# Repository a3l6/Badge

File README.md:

# Hack Canada Badge — v2 (RP2040 + E-Paper)

This was the first serious attempt at the Hack Canada badge before the design was later simplified into the battery-free NFC badges of v3 and v4.

> The main render shows all 51 components placed at their real board positions with the 2.13" e-paper panel mounted on top. Renders are generated from this version's Gerber files (`pcb/prod/gerber/`); colours and the on-screen layout are illustrative.

---

## What it is

Where the later revisions stripped everything down to a passive NFC tag, v2 aimed high: a programmable badge with a screen you could actually put graphics and text on. It's essentially a tiny RP2040 development board in badge form, with an e-paper panel, USB-C for power and programming, and external flash for firmware and assets.

## How it works

```
USB-C ──► RP2040 ──► SPI ──► 2.13" e-paper display (GDEY0213F51)
            │
            ├──► QSPI ──► W25Q32 flash (firmware + images)
            ├──► 12 MHz crystal
            ├──► BOOT + RESET buttons, SWD header
            └──► status LED
```

Plug it in over USB-C, flash firmware to the RP2040 (BOOTSEL/UF2 or SWD), and drive the e-paper display to show a name, schedule, or artwork. The display holds its image with no power, which suits a badge that spends most of its life idle.

## Core components

| Function | Part |
| --- | --- |
| Microcontroller | RP2040 |
| Display | GDEY0213F51 — 2.13" e-paper / E-Ink (SEEKINK panel) |
| Flash | W25Q32JVSSIQ — 32 Mbit (4 MB) SPI/QSPI |
| Clock | 12 MHz crystal (FC4SDCBMF12.0-T1) |
| Power / data | USB Type-C |
| Indicator | VLMC3100-GS08 LED |
| Protection | LESD5D5.0CT1G TVS/ESD diodes |
| Controls | BOOT + RESET buttons, SWD debug header |

## Board

| Spec | Value |
| --- | --- |
| Dimensions | 77.05 × 86.55 mm |
| Layers | 2 |
| Thickness | 1.6 mm |
| Designed in | KiCad 8 |

| Front | Back |
| --- | --- |
|  |  |

### Assembled (parts placed)

The e-paper panel (shown mounted in the main image at the top) connects over the FPC ribbon connector at the upper-left and sits above the board across the open top area, with the RP2040 and power circuitry tucked below it. The on-screen layout in that render is a placeholder mock-up, not artwork from the repo.

## Repository layout (v2 branch)

```
pcb/
├── badge.kicad_pcb / .kicad_sch / .kicad_pro   # main design
├── prod/gerber/                                # Gerbers, drills, gbrjob — ready to fab
├── badge-backups/                              # KiCad auto-backups
├── <component>/                                # per-part symbol/footprint/3D libraries
│   (RP2040, W25Q32, GDEY0213F51, crystal, LEDs, TVS, caps …)
└── assets/                                     # logos
GDEY0213F51.kicad_sym                           # e-paper display symbol
README.md
```

## Building your own

1. **Fabricate:** send `pcb/prod/gerber/` (or `badge-gerbers-and-designs.zip`) to your board house. It's a 2-layer, 1.6 mm board.
2. **Edit:** open `pcb/badge.kicad_pro` in KiCad 8 to modify the layout or schematic.
3. **Assemble & flash:** populate the parts, power over USB-C, and load RP2040 firmware via UF2 (BOOTSEL) or the SWD header. Then drive the GDEY0213F51 over SPI.

## History

v2 → **v3** (pivot to a battery-free NFC badge, adopted from the open "Opentaxus" design) → **v4** (streamlined 4-part NFC badge). See the `v3` and `v4` branches / READMEs.

## License

No license file is included, so all rights are reserved by default. Contact [@a3l6](https://github.com/a3l6) to discuss reuse.

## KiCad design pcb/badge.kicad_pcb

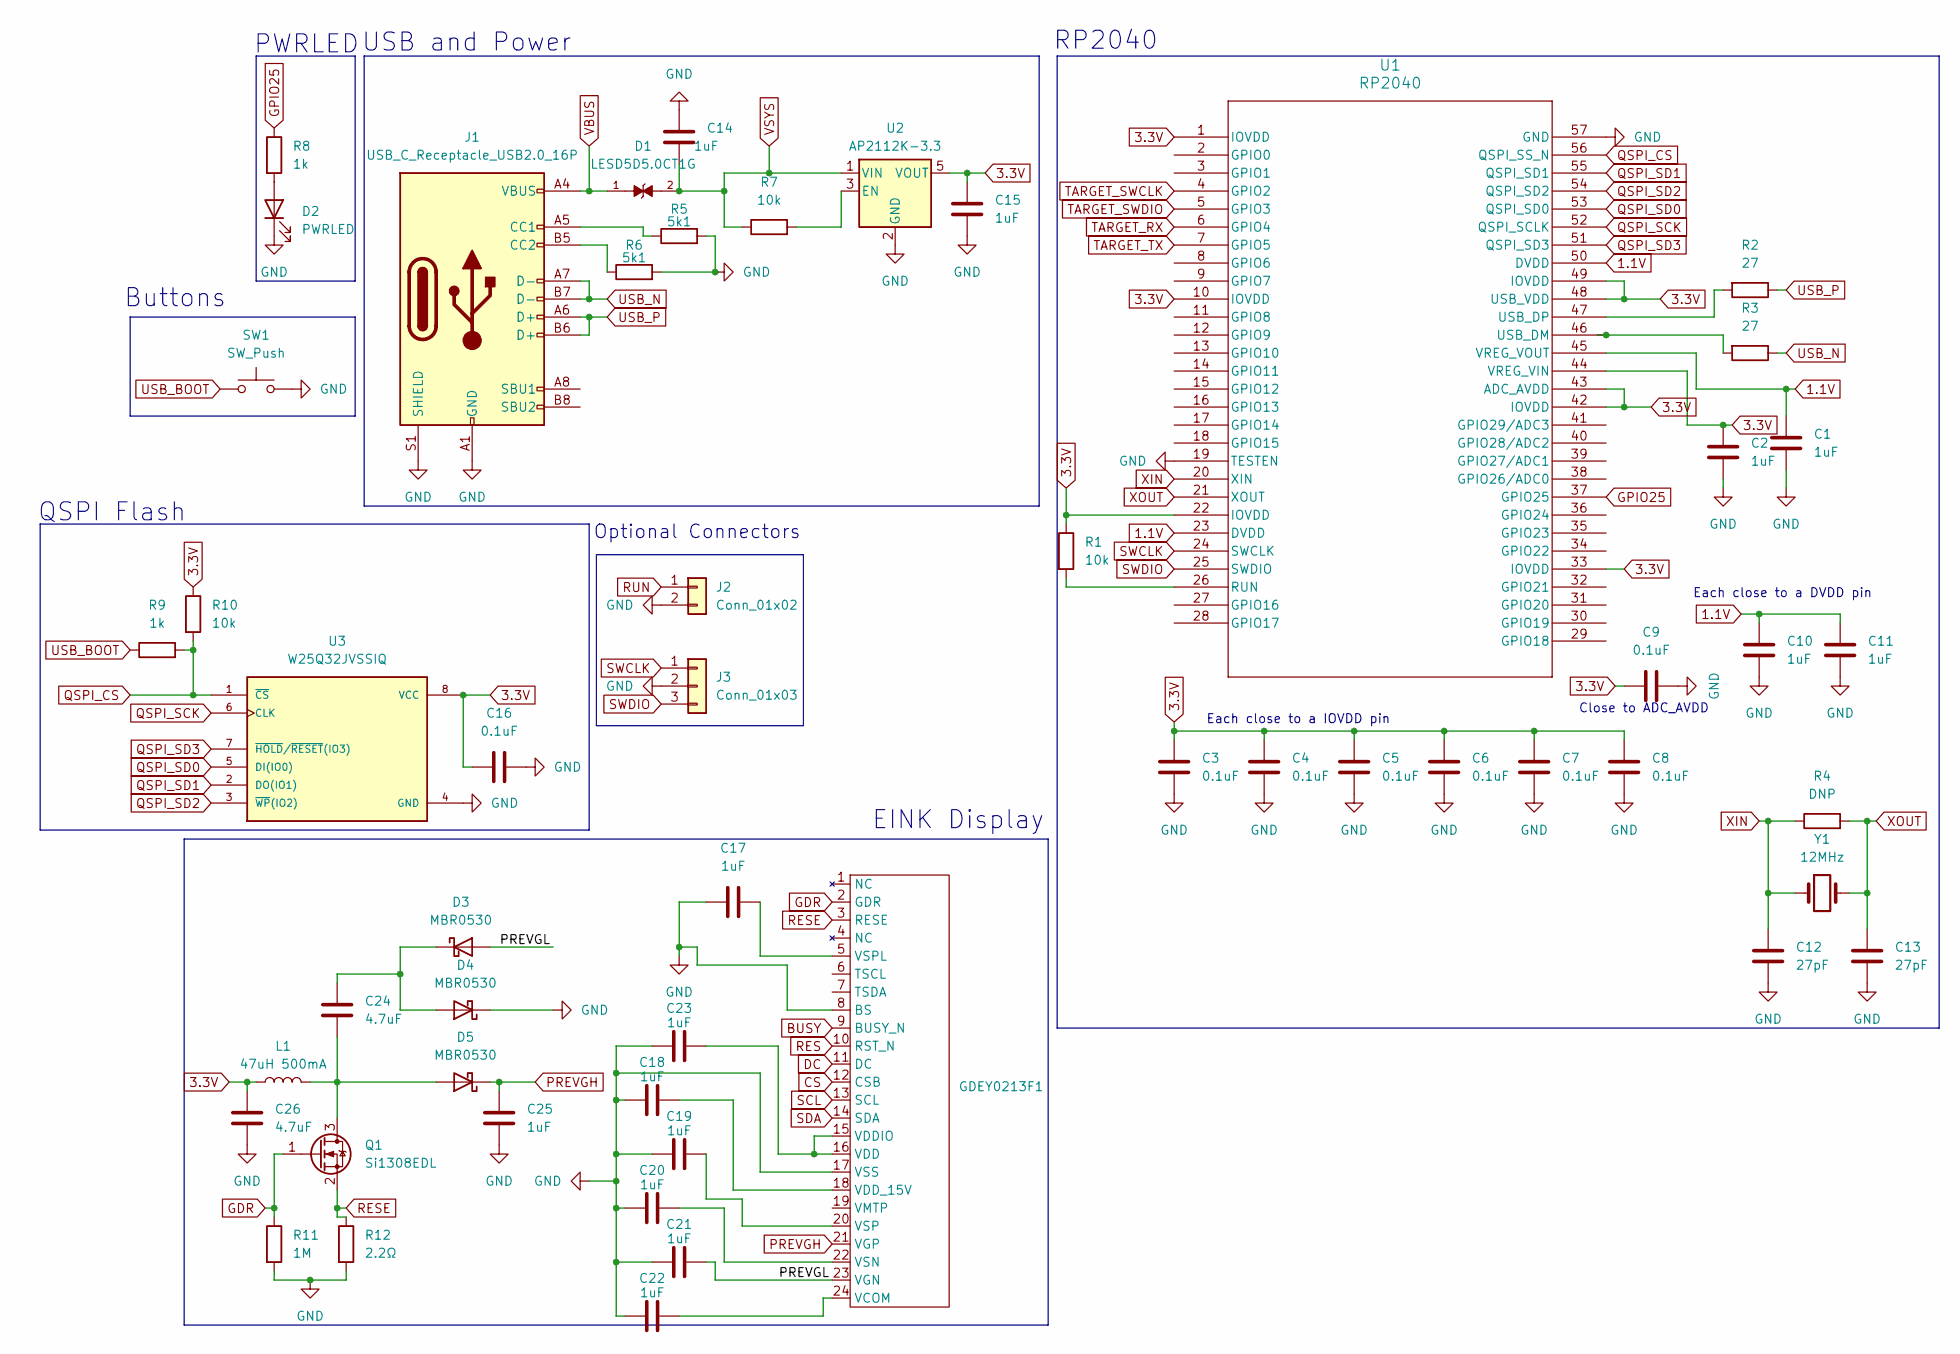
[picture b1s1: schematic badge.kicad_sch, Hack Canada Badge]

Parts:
C1, C2, C10, C11, C14, C15, C17, C18, C19, C20, C21, C22, C23, C25: 1uF; MAJx16
C3, C4, C5, C6, C7, C8, C9, C16: 0.1uF; CAPC2012X94N
C12, C13: 27pF; MAJx16
C24, C26: 4.7uF; CAPC3216X180N
D1: LESD5D5.0CT1G; TVS_LESD5D5.0CT1G; PARTREV O
D2: PWRLED; LEDM3528X185N
D3, D4, D5: MBR0530; D_SOD-123
GDEY0213F1: Hirose_FH12-24S-0.5SH_1x24-1MP_P0.50mm_Horizontal
J1: USB_C_Receptacle_USB2.0_16P; USB_C_Receptacle_Amphenol_12401610E4-2A
J2: Conn_01x02; PinHeader_1x02_P1.00mm_Horizontal
J3: Conn_01x03; PinHeader_1x03_P1.00mm_Horizontal
L1: 47uH 500mA; PinHeader_1x03_P1.00mm_Horizontal
Q1: Si1308EDL; SOT-323_SC-70
R1, R7: 10k; R_01005_0402Metric
R2, R3: 27; R_1210_3225Metric
R4: DNP; R_1206_3216Metric
R5, R6: 5k1; R_1206_3216Metric
R8, R9: 1k; R_0201_0603Metric
R10: 10k; R_0805_2012Metric
R11: 1M; R_2010_5025Metric
R12: 2.2Ω; R_1206_3216Metric
SW1: SW_Push; CAPC3216X180N
U1: RP2040; IC57_RP2040
U2: AP2112K-3.3; SOT-23-5
U3: W25Q32JVSSIQ; SOIC127P790X216-8N; M_PART_NUMBER W25QXX
Y1: 12MHz; CRYSTAL_HC49SDLF_FXT

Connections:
1.1V: C1.1, C10.1, C11.1, U1.23 (DVDD), U1.45 (VREG_VOUT), U1.50 (DVDD)
3.3V: C2.1, C3.1, C4.1, C5.1, C6.1, C7.1, C8.1, C9.1, C15.1, C16.1, C26.1, L1.1, R1.1, R10.1, U1.1 (IOVDD), U1.10 (IOVDD), U1.22 (IOVDD), U1.33 (IOVDD), U1.42 (IOVDD), U1.43 (ADC_AVDD), U1.44 (VREG_VIN), U1.48 (USB_VDD), U1.49 (IOVDD), U2.5 (VOUT), U3.8 (VCC)
/PREVGL: C21.2, D3.2 (A), GDEY0213F1.23 (VGN)
BUSY: GDEY0213F1.9 (BUSY_N)
CS: GDEY0213F1.12 (CSB)
DC: GDEY0213F1.11 (DC)
GDR: GDEY0213F1.2 (GDR), Q1.1 (G), R11.1
GND: C1.2, C2.2, C3.2, C4.2, C5.2, C6.2, C7.2, C8.2, C9.2, C10.2, C11.2, C12.2, C13.2, C14.1, C15.2, C16.2, C17.1, C18.1, C19.1, C20.1, C21.1, C22.1, C23.1, C25.2, C26.2, D2.1 (K), D4.1 (K), GDEY0213F1.8 (BS), GDEY0213F1.17 (VSS), J1.A1 (GND), J1.A12 (GND), J1.B1 (GND), J1.B12 (GND), J1.S1 (SHIELD), J2.2, J3.2, R5.2, R6.2, R11.2, R12.2, SW1.2, U1.19 (TESTEN), U1.57 (GND), U2.2 (GND), U3.4 (GND)
GPIO25: R8.1, U1.37 (GPIO25)
unnamed: D2.2 (A), R8.2
unnamed: C24.1, D3.1 (K), D4.2 (A)
unnamed: C24.2, D5.2 (A), L1.2, Q1.3 (D)
unnamed: C22.2, GDEY0213F1.24 (VCOM)
unnamed: C23.2, GDEY0213F1.15 (VDDIO), GDEY0213F1.16 (VDD)
unnamed: C18.2, GDEY0213F1.18 (VDD_15V)
unnamed: C20.2, GDEY0213F1.22 (VSN)
unnamed: C19.2, GDEY0213F1.20 (VSP)
unnamed: C17.2, GDEY0213F1.5 (VSPL)
unnamed: J1.A5 (CC1), R5.1
unnamed: J1.B5 (CC2), R6.1
unnamed: R1.2, U1.26 (RUN)
unnamed: R3.2, U1.46 (USB_DM)
unnamed: R2.2, U1.47 (USB_DP)
unnamed: R7.2, U2.3 (EN)
PREVGH: C25.1, D5.1 (K), GDEY0213F1.21 (VGP)
QSPI_CS: R9.2, R10.2, U1.56 (QSPI_SS_N), U3.1 (~CS)
QSPI_SCK: U1.52 (QSPI_SCLK), U3.6 (CLK)
QSPI_SD0: U1.53 (QSPI_SD0), U3.5 (DI(IO0))
QSPI_SD1: U1.55 (QSPI_SD1), U3.2 (DO(IO1))
QSPI_SD2: U1.54 (QSPI_SD2), U3.3 (~WP(IO2))
QSPI_SD3: U1.51 (QSPI_SD3), U3.7 (~HOLD/~RESET(IO3))
RES: GDEY0213F1.10 (RST_N)
RESE: GDEY0213F1.3 (RESE), Q1.2 (S), R12.1
RUN: J2.1
SCL: GDEY0213F1.13 (SCL)
SDA: GDEY0213F1.14 (SDA)
SWCLK: J3.1, U1.24 (SWCLK)
SWDIO: J3.3, U1.25 (SWDIO)
TARGET_RX: U1.6 (GPIO4)
TARGET_SWCLK: U1.4 (GPIO2)
TARGET_SWDIO: U1.5 (GPIO3)
TARGET_TX: U1.7 (GPIO5)
USB_BOOT: R9.1, SW1.1
USB_N: J1.A7 (D-), J1.B7 (D-), R3.1
USB_P: J1.A6 (D+), J1.B6 (D+), R2.1
VBUS: D1.1, J1.A4 (VBUS), J1.A9 (VBUS), J1.B4 (VBUS), J1.B9 (VBUS)
VSYS: C14.2, D1.2, R7.1, U2.1 (VIN)
XIN: C12.1, R4.1, U1.20 (XIN), Y1.1
XOUT: C13.1, R4.2, U1.21 (XOUT), Y1.2

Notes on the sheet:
EINK Display
USB and Power
Optional Connectors
Close to ADC_AVDD
Each close to a IOVDD pin
Buttons
Each close to a DVDD pin
RP2040
PWRLED
QSPI Flash

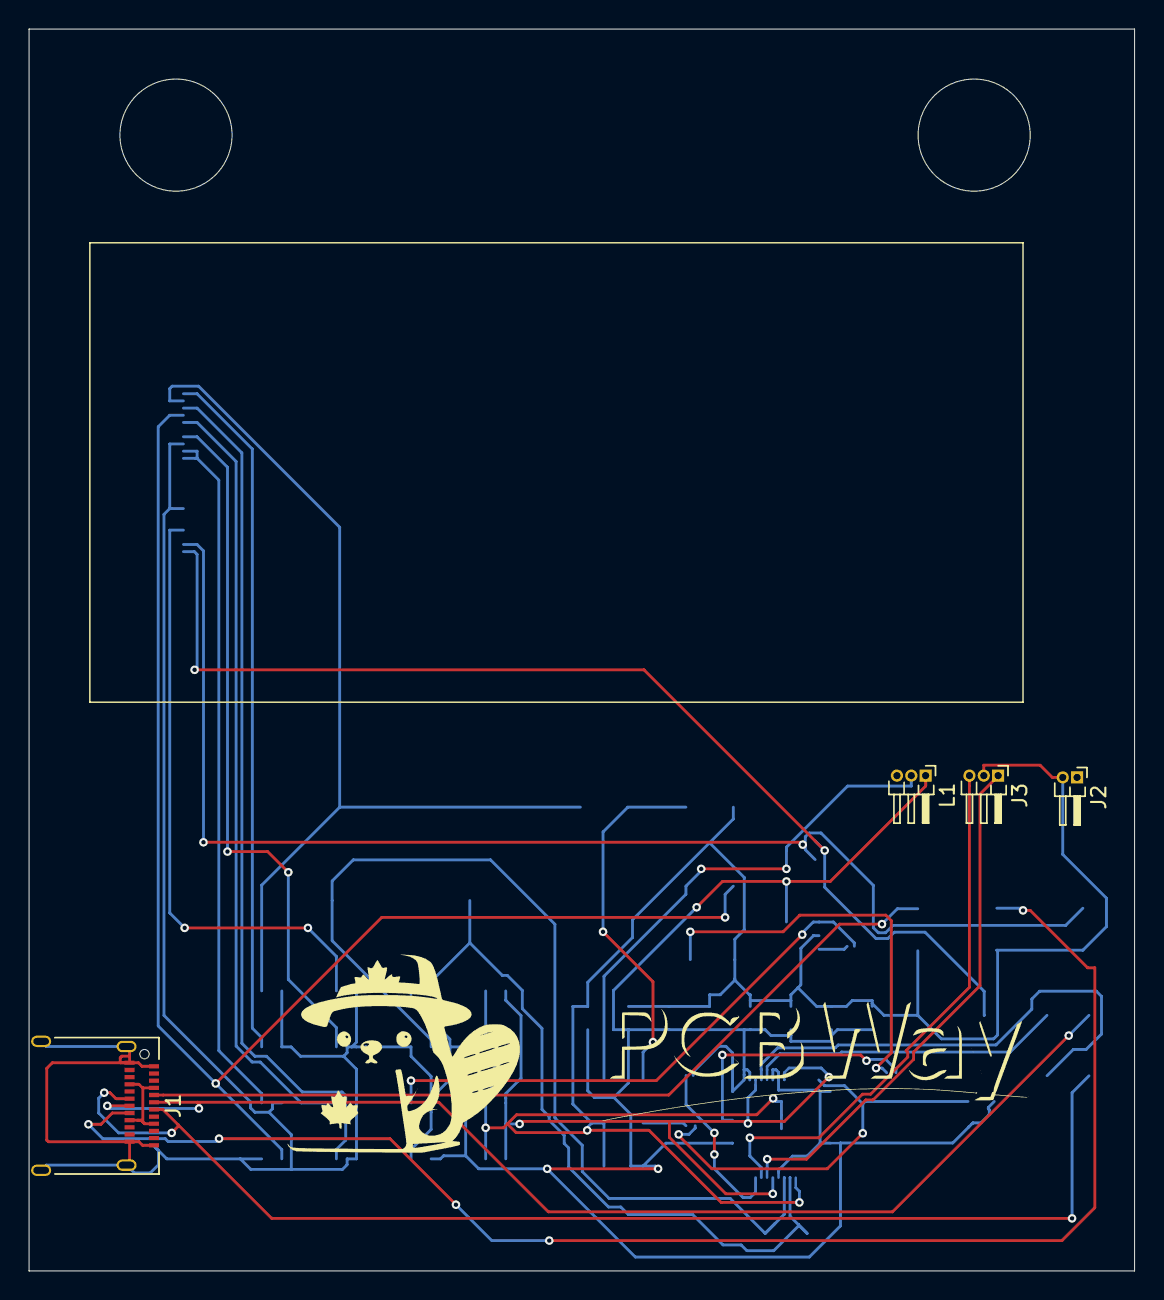
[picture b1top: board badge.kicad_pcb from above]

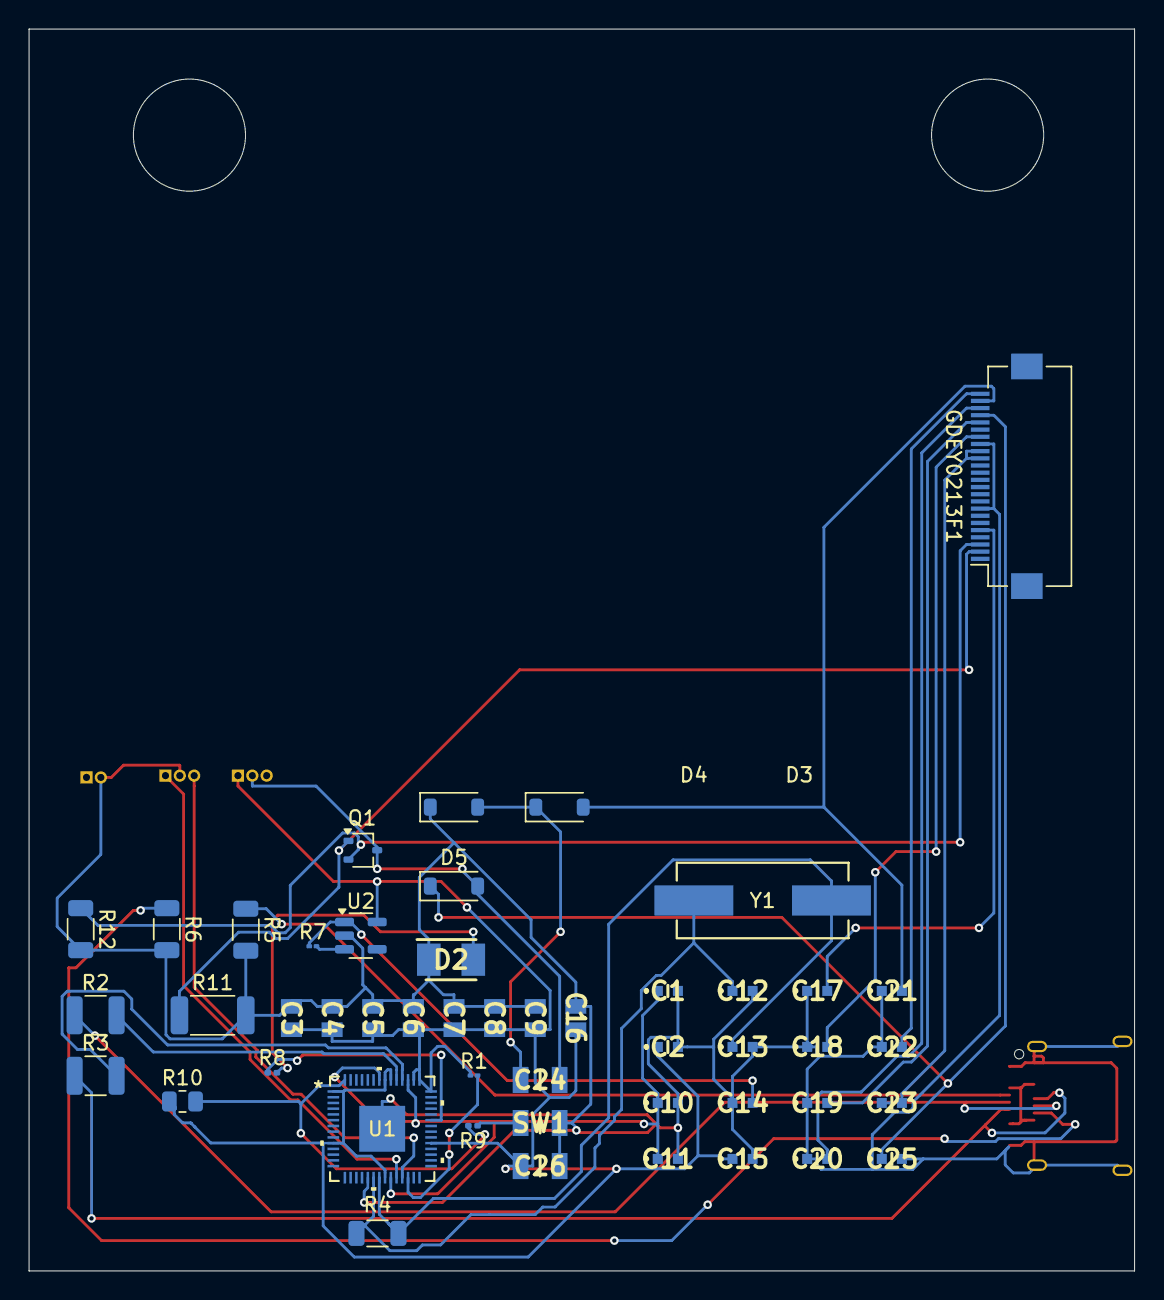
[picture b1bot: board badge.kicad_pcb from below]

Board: 2 copper layers, 77.0 x 86.5 mm, 52 parts (48 on the bottom side), 33 nets.

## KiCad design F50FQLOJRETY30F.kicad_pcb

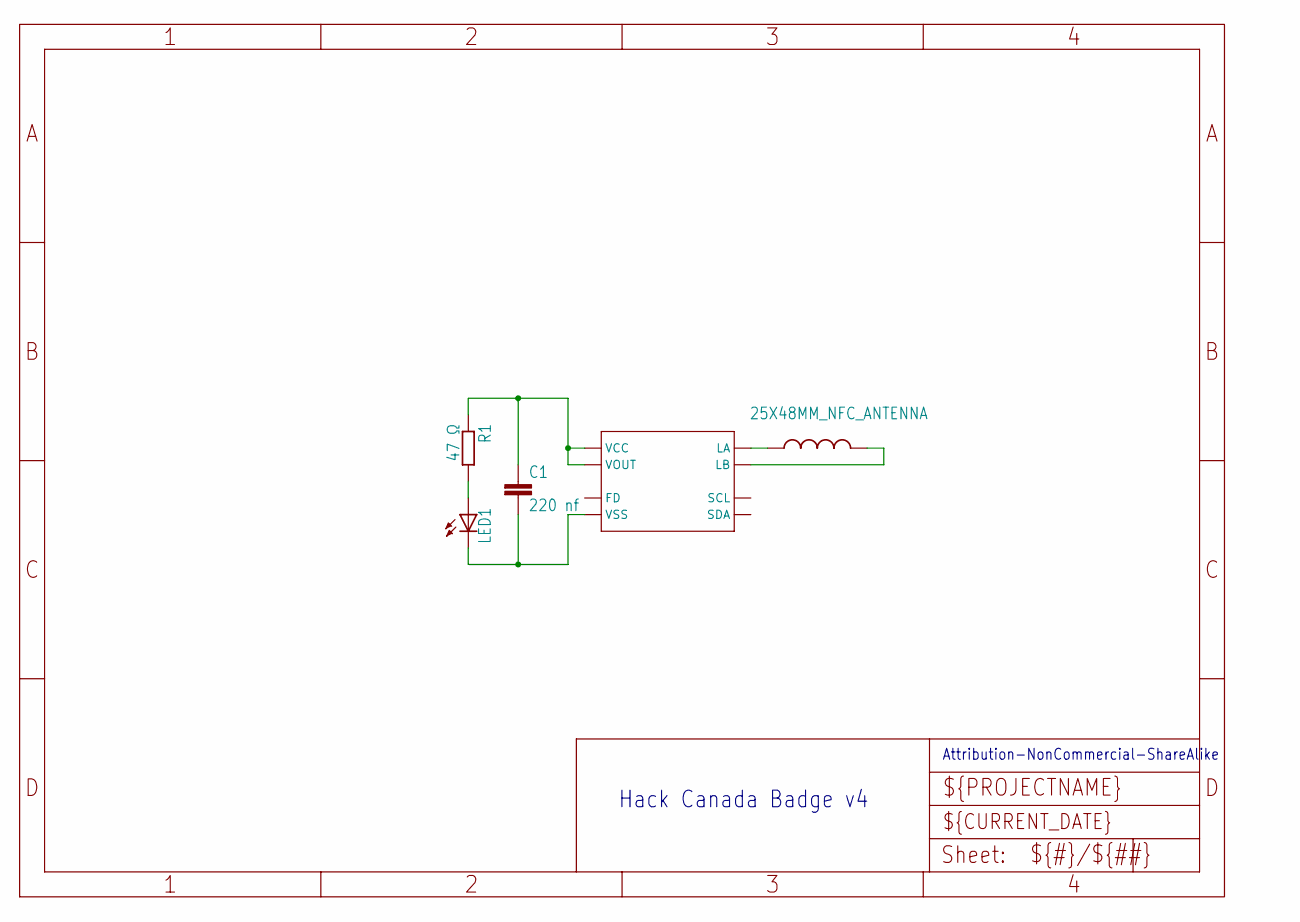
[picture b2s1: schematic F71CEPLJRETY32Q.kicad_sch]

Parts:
ANT0: 25X48MM_NFC_ANTENNA; 25X48MM_NFC
C1: 220 nf; C0603
LED1: LEDSML0805; SML0805
NT3H1101: NT3H; XQFN8
R1: 47 Ω; R0603

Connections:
unnamed: ANT0.P$1, NT3H1101.LB
unnamed: C1.1, NT3H1101.VCC, NT3H1101.VOUT, R1.1
unnamed: LED1.A, R1.2
unnamed: C1.2, LED1.C, NT3H1101.VSS
unnamed: ANT0.P$2, NT3H1101.LA

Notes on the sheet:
Hack Canada Badge v4
Attribution-NonCommercial-ShareAlike

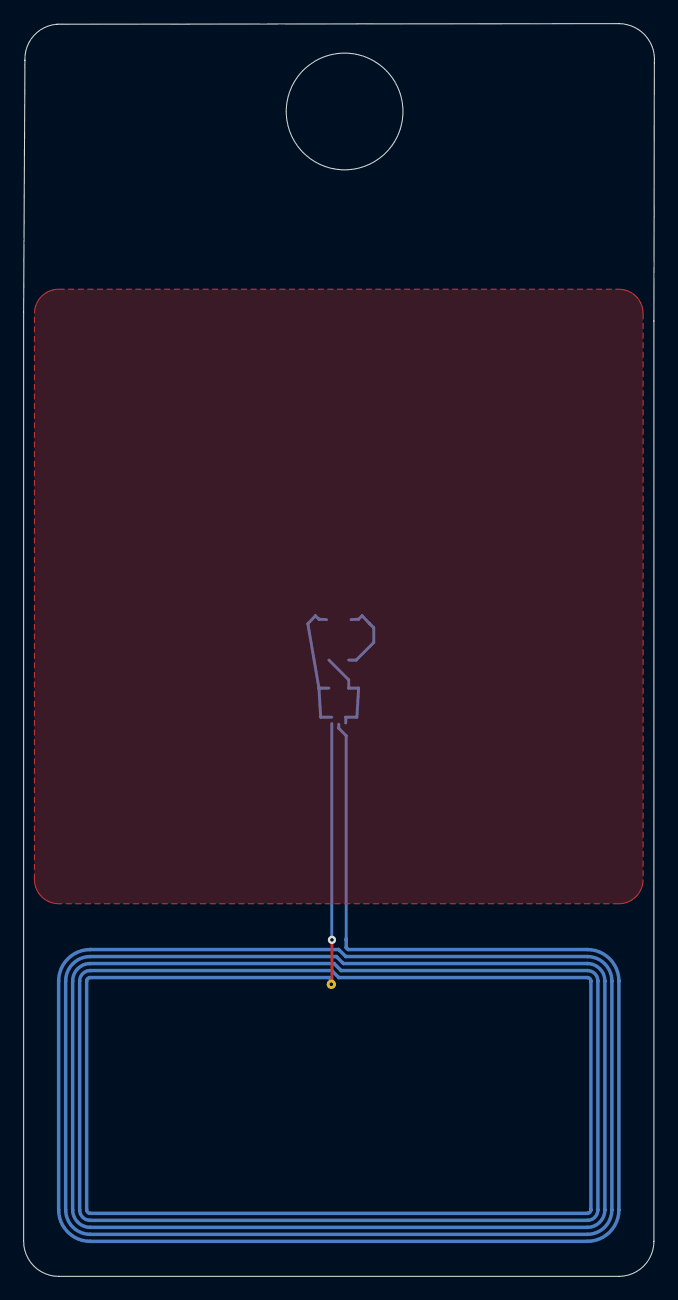
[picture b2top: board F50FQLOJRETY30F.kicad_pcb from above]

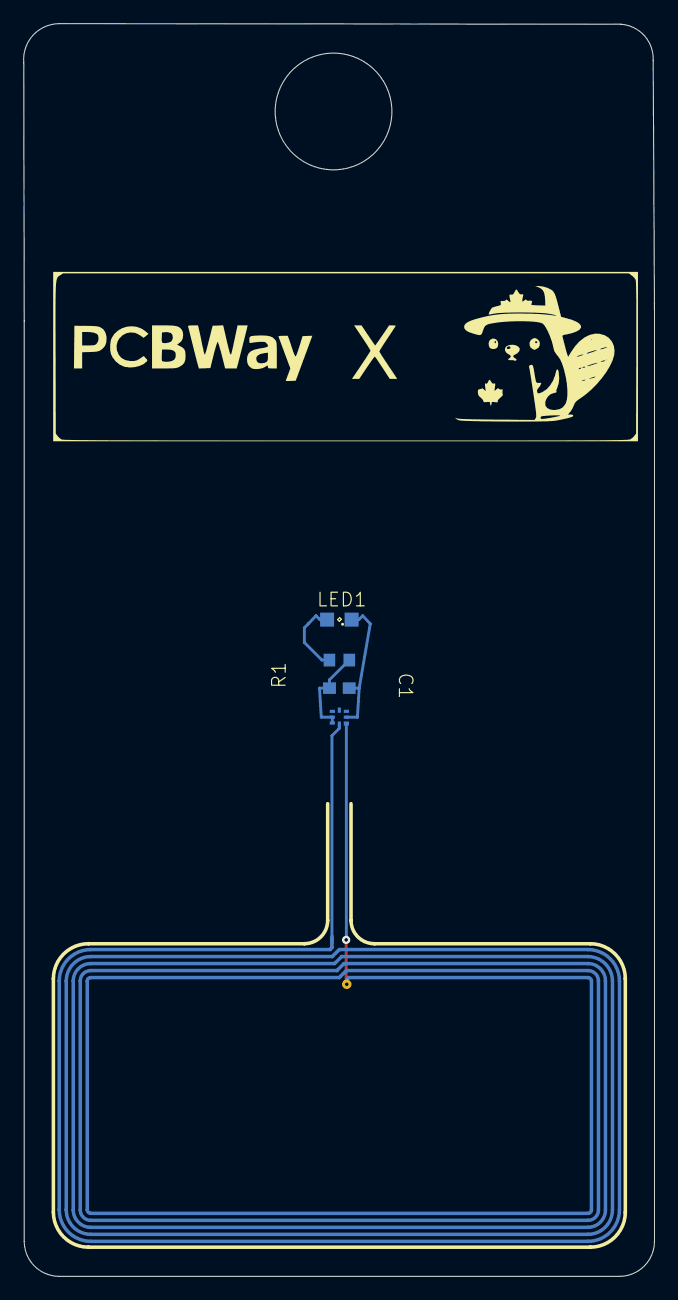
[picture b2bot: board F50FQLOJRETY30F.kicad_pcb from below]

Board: 2 copper layers, 54.0 x 107.3 mm, 5 parts (5 on the bottom side), 5 nets.

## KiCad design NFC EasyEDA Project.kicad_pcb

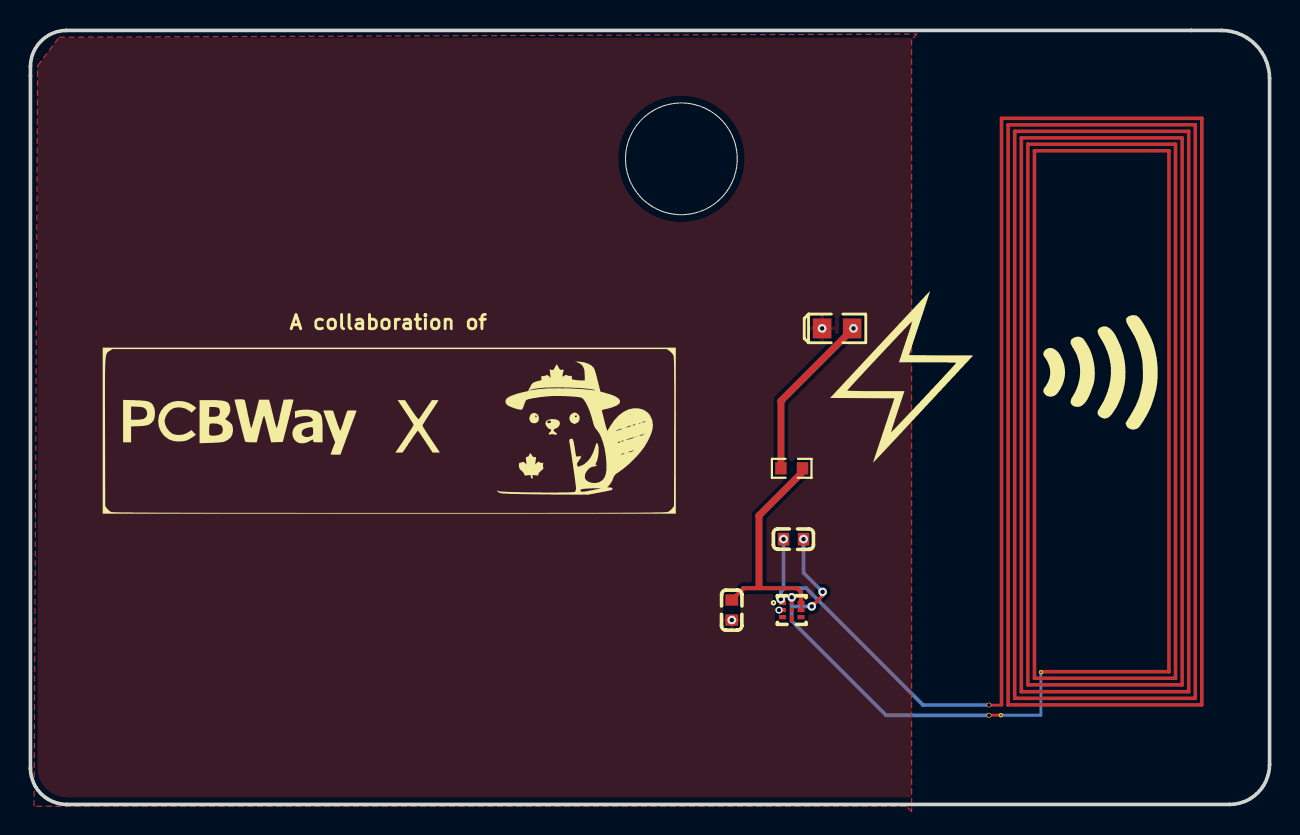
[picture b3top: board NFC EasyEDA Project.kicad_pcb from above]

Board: 2 copper layers, 86.6 x 54.1 mm, 6 parts (0 on the bottom side), 5 nets.

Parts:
1: ANTENNA_NFC_41X14MM_2UH; 25X48MM_NFC_ANTENNA
C1: 220nF; C0603
C2: 18pF; C0603
LED1: LED-0805_B; LED0805_BLUE
R1: 220; R0603
U2: NT3H1101W0FHKH; XQFN-8_L1.6-W1.6-P0.50-BR

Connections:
GND: C1.1, LED1.2, U2.2
LED1_1: LED1.1, R1.1
U2_1: 1.P$1, C2.1, U2.1
U2_8: 1.P$2, C2.2, U2.8
VCC: C1.2, R1.2, U2.6, U2.7

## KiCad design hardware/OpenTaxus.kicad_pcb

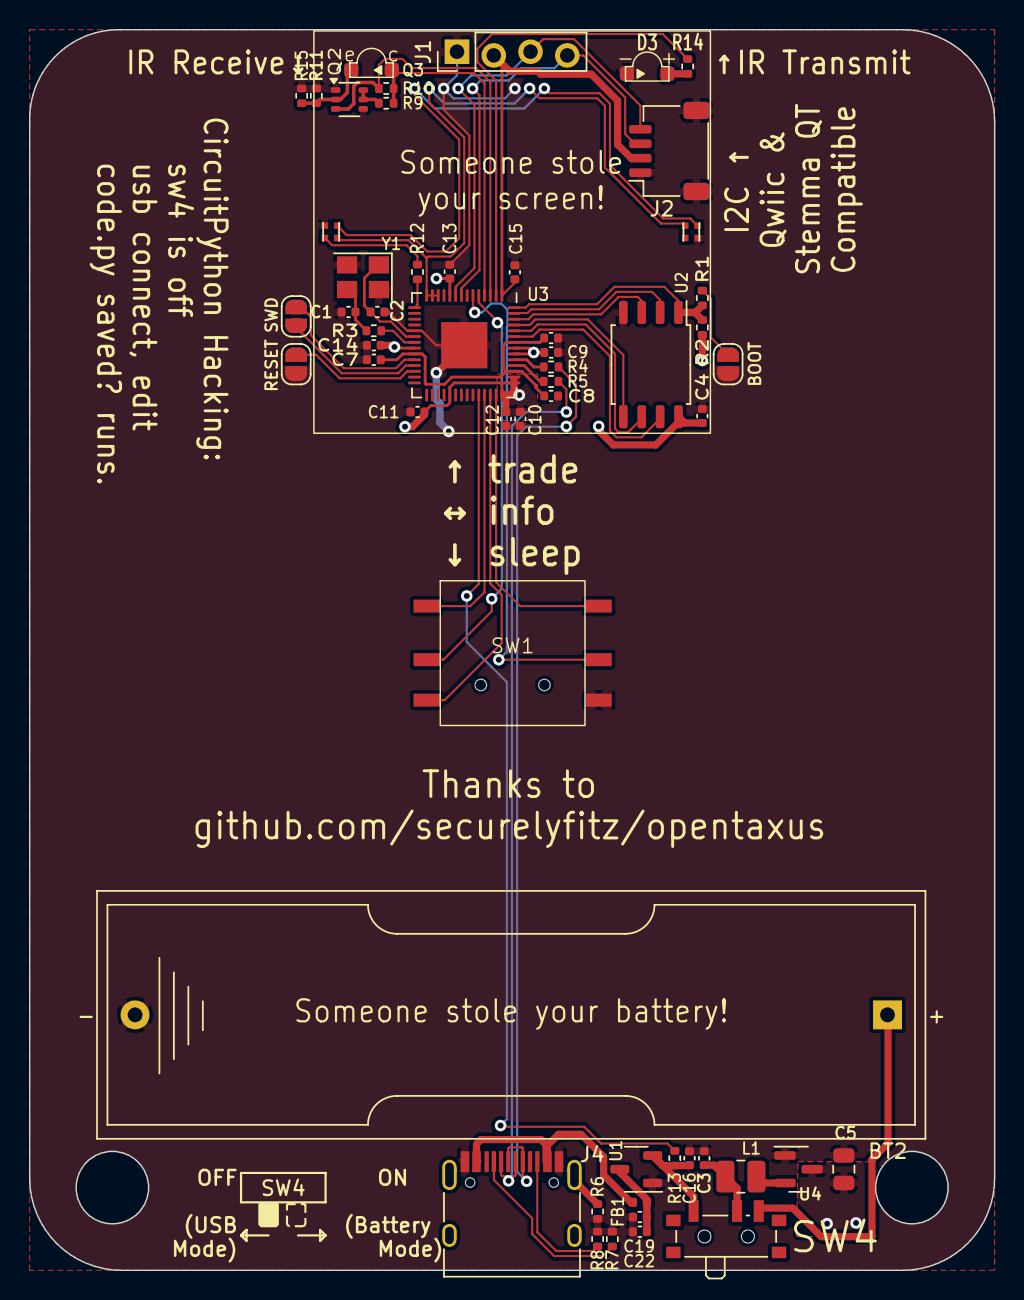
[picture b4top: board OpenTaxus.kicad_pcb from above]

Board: 2 copper layers, 66.7 x 85.7 mm, 54 parts (0 on the bottom side), 47 nets.

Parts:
BT2: AA; BatteryHolder_Keystone_2460_1xAA
C1, C2: 22p; C_0402_1005Metric
C3, C8, C10, C16, C22: 10u; C_0402_1005Metric
C4, C6, C7, C9, C11, C12, C13, C14, C15, C19: 100n; C_0402_1005Metric
C5: 47u; C_0805_2012Metric
D1, D2: WS2812B; LED_WS2812B_PLCC4_1.0x1.0mm
D3: IR12-21C/TR8; IR12-21C-TR8
FB1: 600R; L_0402_1005Metric
J1: OLED; PinHeader_1x04_P2.54mm_Vertical
J2: qwiic; JST_SH_SM04B-SRSS-TB_1x04-1MP_P1.00mm_Horizontal
J3: SWD; SolderJumper-2_P1.3mm_Open_RoundedPad1.0x1.5mm
J4: USB_C_Receptacle_USB2.0; USB_C_Receptacle_HRO_TYPE-C-31-M-12
L1: 10u; L_1008_2520Metric
Q2: BC847BS; SOT-363_SC-70-6
Q3: PT12-21B/TR8; PT12-21B-TR8
R1, R3, R11, R13: 1k; R_0402_1005Metric
R2, R15: DNP; R_0402_1005Metric
R4, R5: 27; R_0402_1005Metric
R6: 1M; R_0402_1005Metric
R7, R8: 5k1; R_0402_1005Metric
R9, R10: 200k; R_0402_1005Metric
R12, R14: 220; R_0402_1005Metric
SW1: dpad; 10x10x10x9-6P-WX
SW2: USB_BOOT; SolderJumper-2_P1.3mm_Open_RoundedPad1.0x1.5mm
SW3: RESET; SolderJumper-2_P1.3mm_Open_RoundedPad1.0x1.5mm
SW4: SW_SPDT; SW_SPDT_PCM12
U1: HE6206-33NR; SOT-23-3
U2: W25Q128JVS; SOIC-8_5.23x5.23mm_P1.27mm
U3: RP2040; QFN-56-1EP_7x7mm_P0.4mm_EP3.2x3.2mm
U4: XT1861B332MR-G; SOT-23
Y1: YSX321SL; Crystal_SMD_3225-4Pin_3.2x2.5mm

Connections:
+1V1: C6.1, C7.1, C8.1, U3.23 (DVDD), U3.45 (VREG_VOUT), U3.50 (DVDD)
+3V3: C4.1, C5.1, C9.1, C10.1, C11.1, C12.1, C13.1, C14.1, C15.1, J1.2, J2.2, R2.1, U2.8 (VCC), U3.1 (IOVDD), U3.10 (IOVDD), U3.22 (IOVDD), U3.33 (IOVDD), U3.42 (IOVDD), U3.43 (ADC_AVDD), U3.44 (VREG_IN), U3.48 (USB_VDD), U3.49 (IOVDD), U4.3 (VOUT)
+VSW: C3.1, L1.1, SW4.2 (B)
/GPIO0/TX: R14.1, U3.2 (GPIO0)
/GPIO1/RX: Q2.3 (C2), R10.2, U3.3 (GPIO1)
/GPIO2/SD: Q3.1 (C), R9.1, R10.1, U3.4 (GPIO2)
/GPIO3/L: SW1.2 (L), U3.5 (GPIO3)
/GPIO4/R: SW1.5 (R), U3.6 (GPIO4)
/GPIO6/SDA: J1.4, J2.3, U3.8 (GPIO6)
/GPIO7/SCL: J1.3, J2.4, U3.9 (GPIO7)
/GPIO11/NEO_PWR: D1.2 (VDD), D2.2 (VDD), U3.12 (GPIO9), U3.13 (GPIO10), U3.14 (GPIO11)
/GPIO12/NEOPIX: R12.1, U3.15 (GPIO12)
/GPIO26_ADC0/USB_DET: R13.1, U3.38 (GPIO26_ADC0)
/GPIO27_ADC1/U: SW1.1 (U), U3.39 (GPIO27_ADC1)
/GPIO28_ADC2/D: SW1.3 (D), U3.40 (GPIO28_ADC2)
/GPIO29_ADC3/X: SW1.6 (X), U3.41 (GPIO29_ADC3)
/QSPI_SCLK: U2.6 (CLK), U3.52 (QSPI_SCLK)
/QSPI_SD0: U2.5 (DI(IO0)), U3.53 (QSPI_SD0)
/QSPI_SD1: U2.2 (DO(IO1)), U3.55 (QSPI_SD1)
/QSPI_SD2: U2.3 (IO2), U3.54 (QSPI_SD2)
/QSPI_SD3: U2.7 (IO3), U3.51 (QSPI_SD3)
/QSPI_SS: R1.1, R2.2, U2.1 (~CS), U3.56 (QSPI_SS)
/RUN: SW3.1, U3.26 (RUN)
/SHIELD: J4.S1 (SHIELD), R6.2
/SWCLK: J3.2, U3.24 (SWCLK)
/SWD: J3.1, U3.25 (SWD)
/USB_D+: J4.A6 (D+), J4.B6 (D+), R4.2
/USB_D-: J4.A7 (D-), J4.B7 (D-), R5.1
/VBATT: BT2.1 (+), SW4.3 (C)
/VBUS: FB1.2, J4.A4 (VBUS), J4.A9 (VBUS), J4.B4 (VBUS), J4.B9 (VBUS)
/VREG: C16.1, R13.2, SW4.1 (A), U1.2 (VO)
/VUSB: C19.1, C22.1, FB1.1, U1.3 (VI)
/XIN: C2.2, U3.20 (XIN), Y1.1
/XOUT: R3.1, U3.21 (XOUT)
/~USB_BOOT: R1.2, SW2.1
GND: BT2.2 (-), C1.2, C2.1, C3.2, C4.2, C5.2, C6.2, C7.2, C8.2, C9.2, C10.2, C11.2, C12.2, C13.2, C14.2, C15.2, C16.2, C19.2, C22.2, D1.3 (VSS), D2.3 (VSS), D3.2 (K), J1.1, J2.1, J2.MP (MountPin), J4.A1 (GND), J4.A12 (GND), J4.B1 (GND), J4.B12 (GND), Q2.1 (E1), Q2.4 (E2), R6.1, R7.1, R8.2, R11.1, R15.1, SW1.4 (C), SW2.2, SW3.2, U1.1 (GND), U2.4 (GND), U3.19 (TESTEN), U3.57 (GND), U4.1 (GND), Y1.2, Y1.4
unnamed: C1.1, R3.2, Y1.3
unnamed: D1.4 (DIN), R12.2
unnamed: D1.1 (DOUT), D2.4 (DIN)
unnamed: D3.1 (A), R14.2
unnamed: J4.A5 (CC1), R7.2
unnamed: J4.B5 (CC2), R8.1
unnamed: Q2.2 (B1), Q3.2 (E), R11.2, R15.2
unnamed: Q2.5 (B2), Q2.6 (C1), R9.2
unnamed: R5.2, U3.46 (USB_DM)
unnamed: R4.1, U3.47 (USB_DP)
unnamed: L1.2, U4.2 (SW)

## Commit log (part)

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2024-10-26 Began routing for esp32
2024-10-29 Finished USB-C and ESP32 schematic
2024-10-31 Made symbol for GDEY0213F51
2024-11-01 Began changing to rp2040
2024-11-05 Beginning to get footprints
2024-11-06 Began schematic
2024-11-06 Saving before autorouting
2024-11-06 More footprints
2024-11-07 Finished routing
2024-12-08 Added sketches
2025-01-15 Adopted Opentaxus badge
2025-02-04 V3 done?
2025-02-08 V4 done and submitted
